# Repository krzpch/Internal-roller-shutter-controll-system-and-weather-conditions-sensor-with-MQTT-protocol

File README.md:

# Internal-roller-shutter-controll-system-and-weather-conditions-sensor-with-MQTT-protocol

This project is a part of smart home system based on MQTT protocol for comunication.
Weather condtions sensor is battery operated. To comunicate with shutter controll it uses Bluetooth Low Energy.
Shutter controll comunicates by Wi-Fi with MQTT Broker. It also works as a gate between Broker and Weather conditions sensor.

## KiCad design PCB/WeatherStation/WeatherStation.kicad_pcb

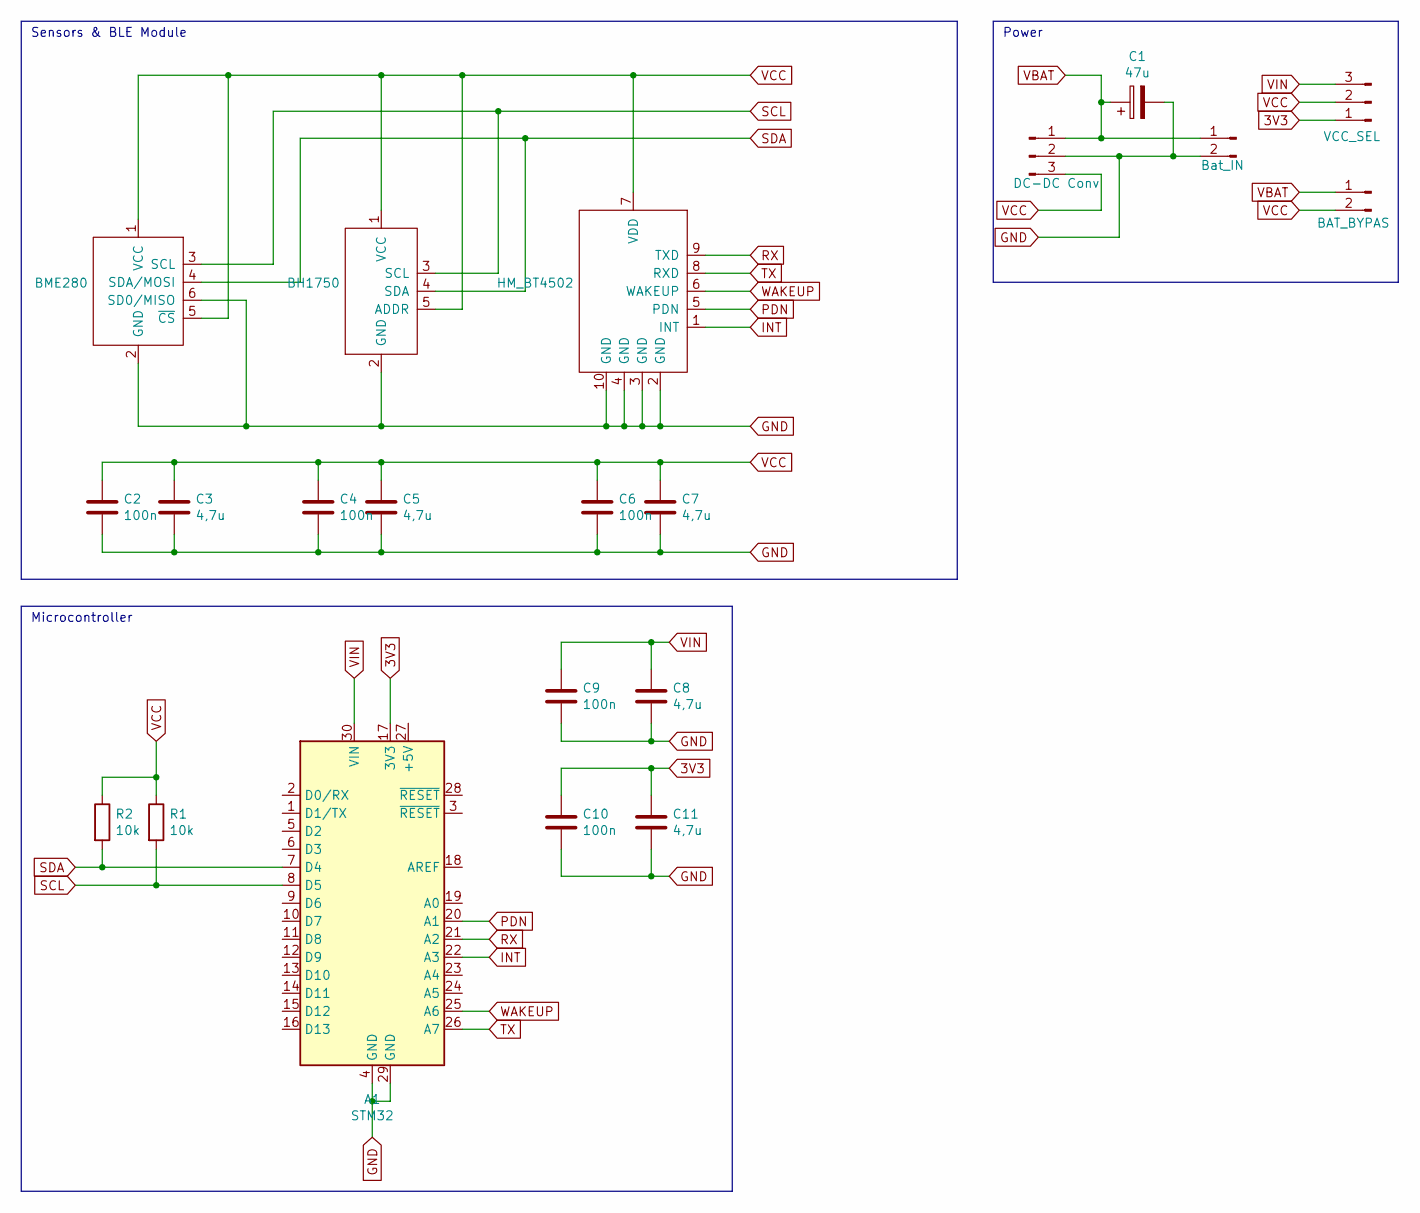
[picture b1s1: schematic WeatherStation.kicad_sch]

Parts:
A1: STM32; Arduino_Nano
BH1750: BH1750; PinHeader_1x05_P2.54mm_Vertical
BME280: BME280; PinHeader_1x06_P2.54mm_Vertical
C1: 47u; CP_Radial_D5.0mm_P2.00mm
C2, C4, C6, C9, C10: 100n; C_1206_3216Metric_Pad1.33x1.80mm_HandSolder
C3, C5, C7, C8, C11: 4,7u; C_1206_3216Metric_Pad1.33x1.80mm_HandSolder
HM_BT4502: HM_BT4502; HM-BT4502
J1: BAT_BYPAS; PinHeader_1x02_P2.54mm_Vertical
J2: VCC_SEL; PinHeader_1x03_P2.54mm_Vertical
J3: DC-DC Conv; PinHeader_1x03_P2.54mm_Vertical
J4: Bat_IN; PinHeader_1x02_P2.54mm_Vertical
R1, R2: 10k; R_Axial_DIN0207_L6.3mm_D2.5mm_P7.62mm_Horizontal

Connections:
3V3: A1.17 (3V3), C10.1, C11.1, J2.1
GND: A1.4 (GND), A1.29 (GND), BH1750.2 (GND), BME280.2 (GND), BME280.6 (SD0/MISO), C1.2, C2.2, C3.2, C4.2, C5.2, C6.2, C7.2, C8.2, C9.2, C10.2, C11.2, HM_BT4502.2 (GND), HM_BT4502.3 (GND), HM_BT4502.4 (GND), HM_BT4502.10 (GND), J3.2, J4.2
INT: A1.22 (A3), HM_BT4502.1 (INT)
PDN: A1.20 (A1), HM_BT4502.5 (PDN)
RX: A1.21 (A2), HM_BT4502.9 (TXD)
SCL: A1.8 (D5), BH1750.3 (SCL), BME280.3 (SCL), R1.2
SDA: A1.7 (D4), BH1750.4 (SDA), BME280.4 (SDA/MOSI), R2.2
TX: A1.26 (A7), HM_BT4502.8 (RXD)
VBAT: C1.1, J1.1, J3.1, J4.1
VCC: BH1750.1 (VCC), BH1750.5 (ADDR), BME280.1 (VCC), BME280.5 (~CS), C2.1, C3.1, C4.1, C5.1, C6.1, C7.1, HM_BT4502.7 (VDD), J1.2, J2.2, J3.3, R1.1, R2.1
VIN: A1.30 (VIN), C8.1, C9.1, J2.3
WAKEUP: A1.25 (A6), HM_BT4502.6 (WAKEUP)

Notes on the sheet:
Power
Microcontroller
Sensors & BLE Module

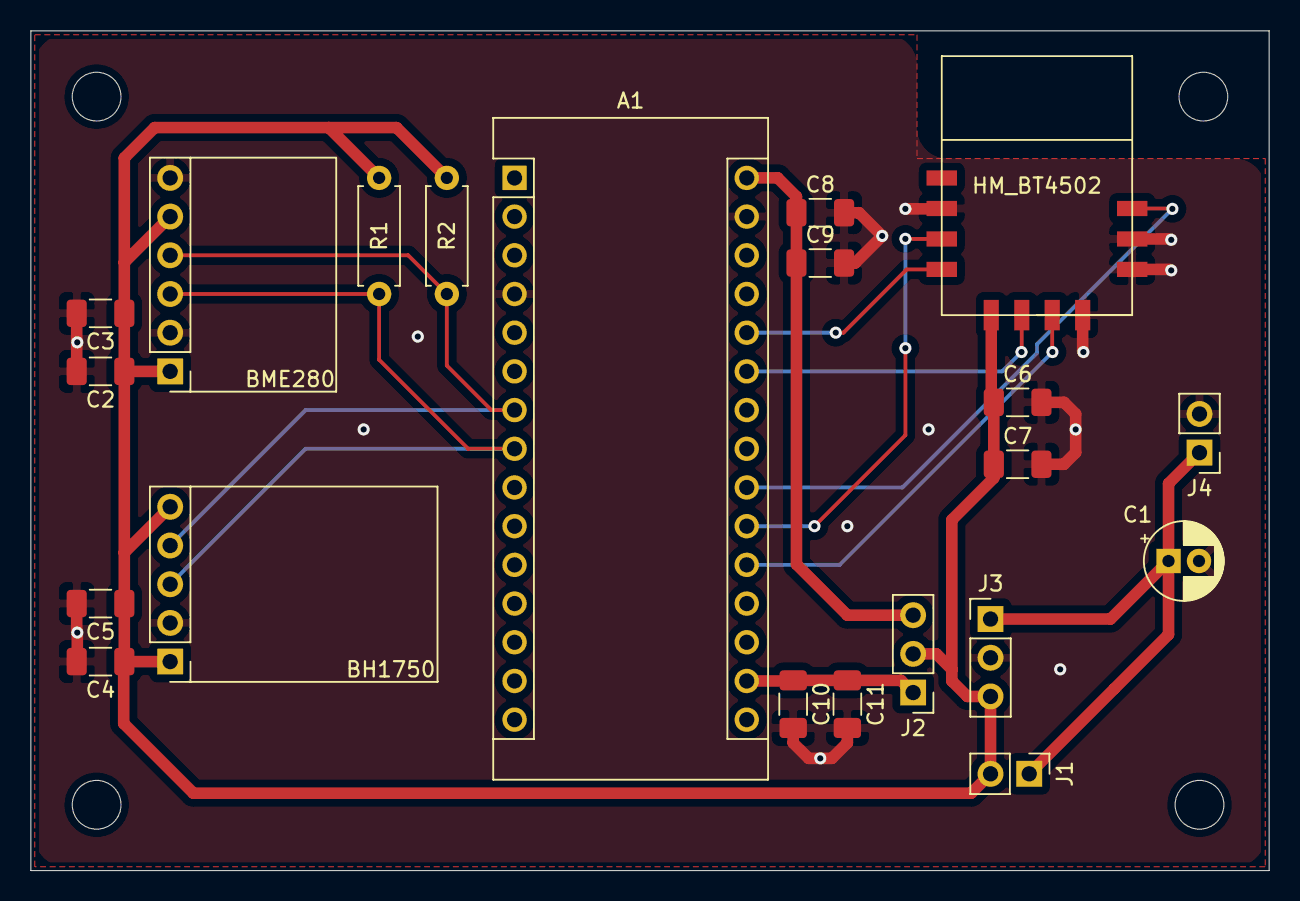
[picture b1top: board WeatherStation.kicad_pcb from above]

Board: 2 copper layers, 81.3 x 55.1 mm, 21 parts (0 on the bottom side), 12 nets.

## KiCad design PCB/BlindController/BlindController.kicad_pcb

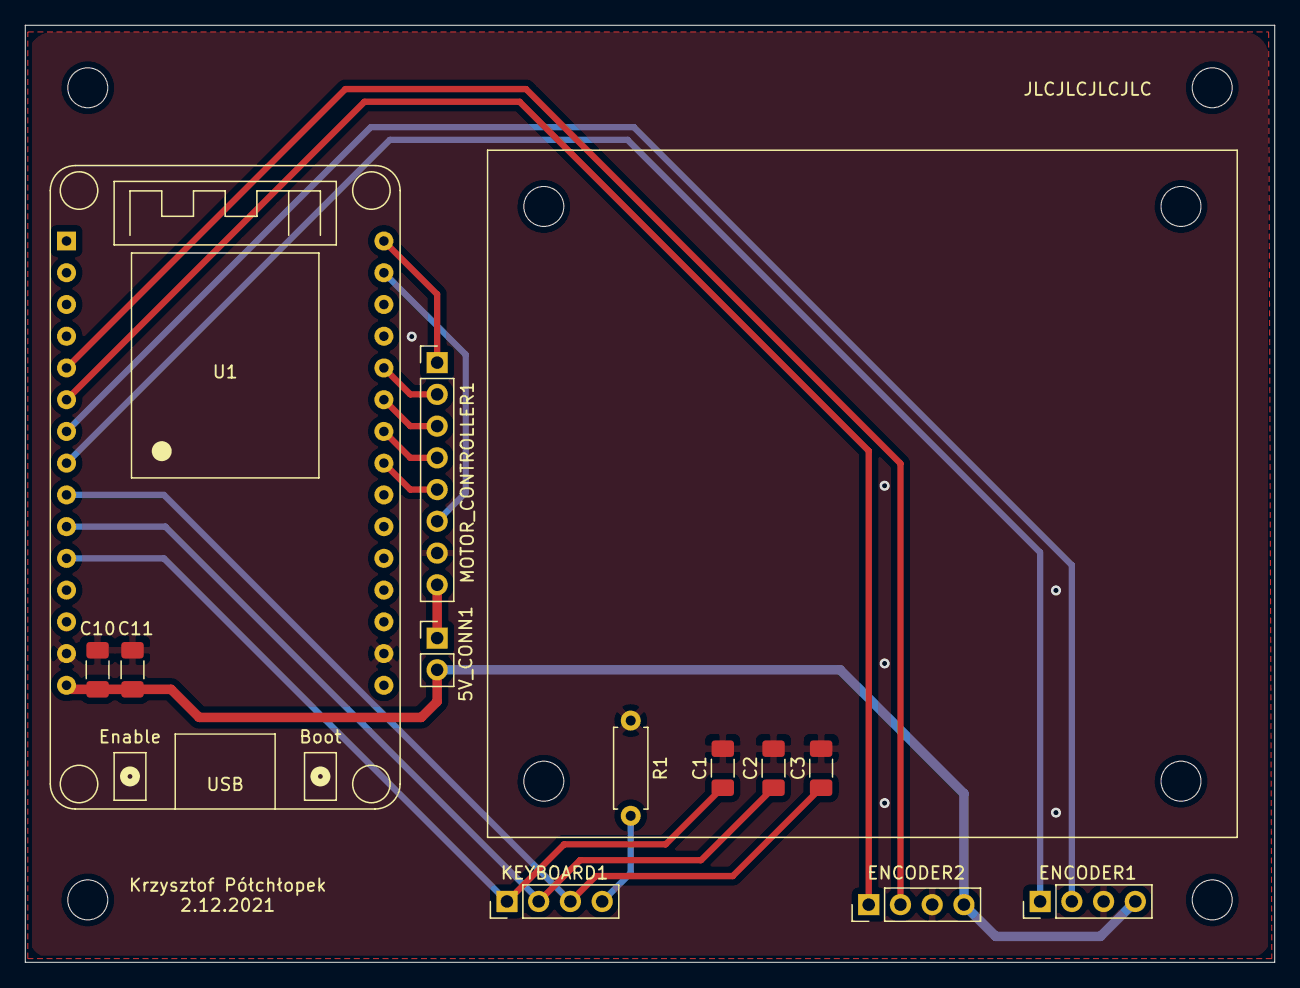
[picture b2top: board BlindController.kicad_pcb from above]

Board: 2 copper layers, 100.0 x 75.0 mm, 12 parts (0 on the bottom side), 17 nets.

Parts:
5V_CONN1: 5V_CONN; PinHeader_1x02_P2.54mm_Vertical
C1, C2, C3, C10: 100n; C_1206_3216Metric_Pad1.33x1.80mm_HandSolder
C11: 4,7u; C_1206_3216Metric_Pad1.33x1.80mm_HandSolder
ENCODER1, ENCODER2: Conn_01x04_Male; PinHeader_1x04_P2.54mm_Vertical
KEYBOARD1: Conn_01x04_Male; PinHeader_1x04_P2.54mm_Vertical
MOTOR_CONTROLLER1: Conn_01x08_Male; PinHeader_1x08_P2.54mm_Vertical
R1: 10k; R_Axial_DIN0207_L6.3mm_D2.5mm_P7.62mm_Horizontal
U1: ESP32_DevKit_V1_DOIT; esp32_devkit_v1_doit

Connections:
5V: 5V_CONN1.2, C10.1, C11.1, ENCODER1.4, ENCODER2.4, U1.15
A_ENC1: ENCODER1.1, U1.8
A_ENC2: ENCODER1.2, U1.7
A_IN1: MOTOR_CONTROLLER1.2, U1.26
A_IN2: MOTOR_CONTROLLER1.3, U1.25
A_PWM: MOTOR_CONTROLLER1.1, U1.30
BUT1: C1.1, KEYBOARD1.1, U1.11
BUT2: C2.1, KEYBOARD1.2, U1.10
BUT3: C3.1, KEYBOARD1.3, U1.9
B_ENC1: ENCODER2.1, U1.6
B_ENC2: ENCODER2.2, U1.5
B_IN1: MOTOR_CONTROLLER1.4, U1.24
B_IN2: MOTOR_CONTROLLER1.5, U1.23
B_PWM: MOTOR_CONTROLLER1.6, U1.29
GND: C1.2, C2.2, C3.2, C10.2, C11.2, ENCODER1.3, ENCODER2.3, MOTOR_CONTROLLER1.7, R1.1, U1.14, U1.17
unnamed: 5V_CONN1.1, MOTOR_CONTROLLER1.8
unnamed: KEYBOARD1.4, R1.2

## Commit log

2022-02-09 Added all
